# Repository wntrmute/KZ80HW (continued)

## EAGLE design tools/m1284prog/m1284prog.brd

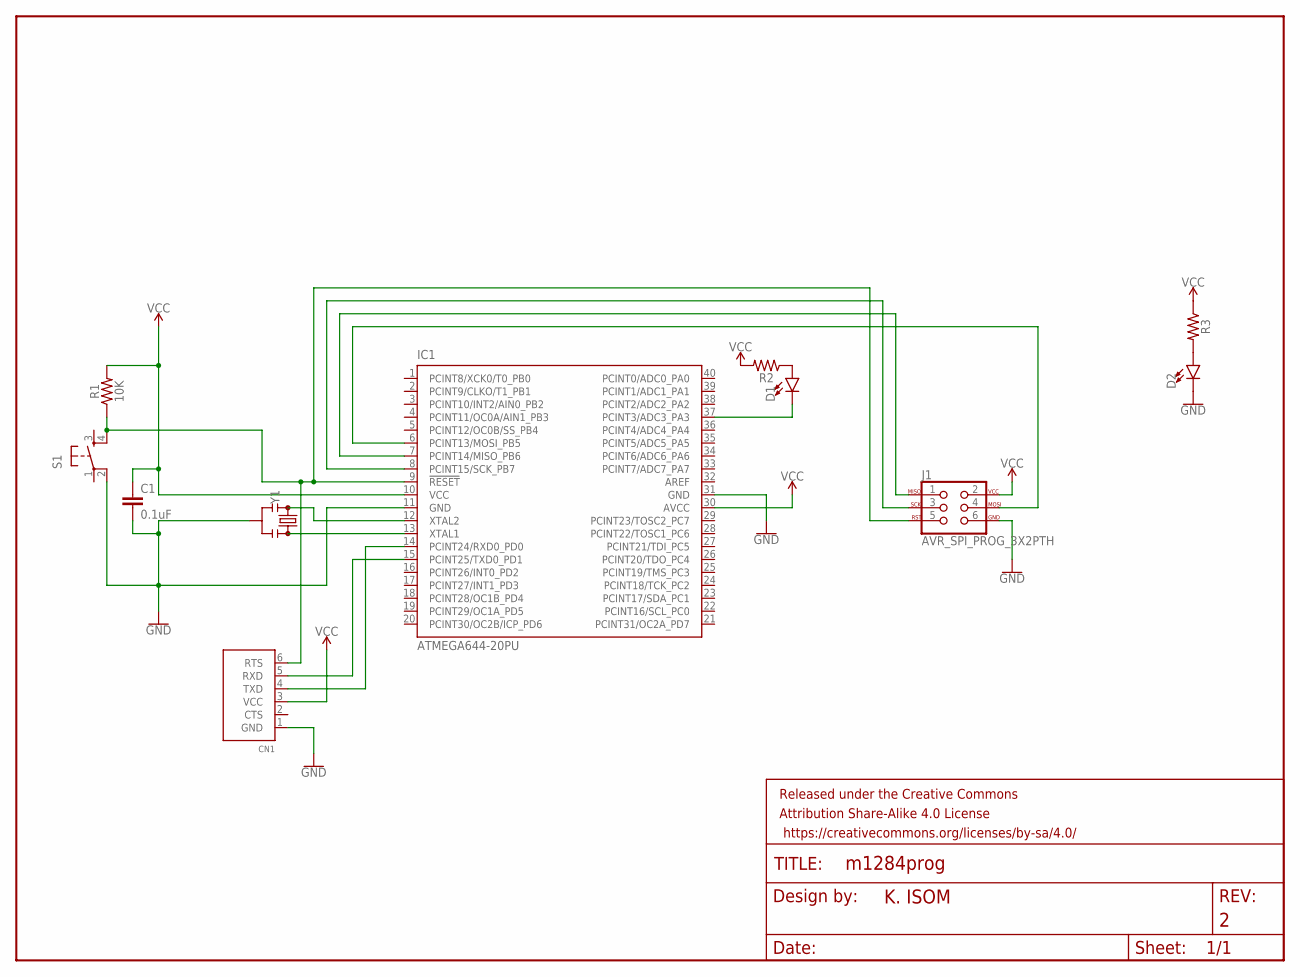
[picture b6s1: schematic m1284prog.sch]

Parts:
C1: 0.1uF; C2.5-3
CN1: FTDIUSBCABLE; 1X06_ROUND
D1, D2: LED3MM; LED_3MM
FRAME1: FRAME-LETTER; CREATIVE_COMMONS
IC1: ATMEGA644-20PU; DIL40
J1: AVR_SPI_PROG_3X2PTH; 2X3
R1: 10K; AXIAL-0.3
R2, R3: AXIAL-0.3
S1: TAC_SWITCHPTH; TACTILE-PTH
Y1: RESONATORPTH-7.6X3.8; RESONATOR-PTH-7.6X3.8

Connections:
GND: C1.2, CN1.1 (GND), D2.K (C), IC1.11 (GND), IC1.31 (GND), J1.6, S1.2, Y1.2
unnamed: IC1.12 (XTAL2), Y1.1
unnamed: IC1.13 (XTAL1), Y1.3
unnamed: IC1.6 (PCINT13/MOSI_PB5), J1.4
unnamed: CN1.6 (RTS), IC1.9 (!RESET), J1.5, R1.P$1 (1), S1.4
unnamed: IC1.7 (PCINT14/MISO_PB6), J1.1
unnamed: IC1.8 (PCINT15/SCK_PB7), J1.3
unnamed: D1.K (C), IC1.37 (PCINT3/ADC3_PA3)
unnamed: D1.A, R2.P$1 (1)
unnamed: CN1.4 (TXD), IC1.14 (PCINT24/RXD0_PD0)
unnamed: CN1.5 (RXD), IC1.15 (PCINT25/TXD0_PD1)
unnamed: D2.A, R3.P$2 (2)
VCC: C1.1, CN1.3 (VCC), IC1.10 (VCC), IC1.30 (AVCC), J1.2, R1.P$2 (2), R2.P$2 (2), R3.P$1 (1)

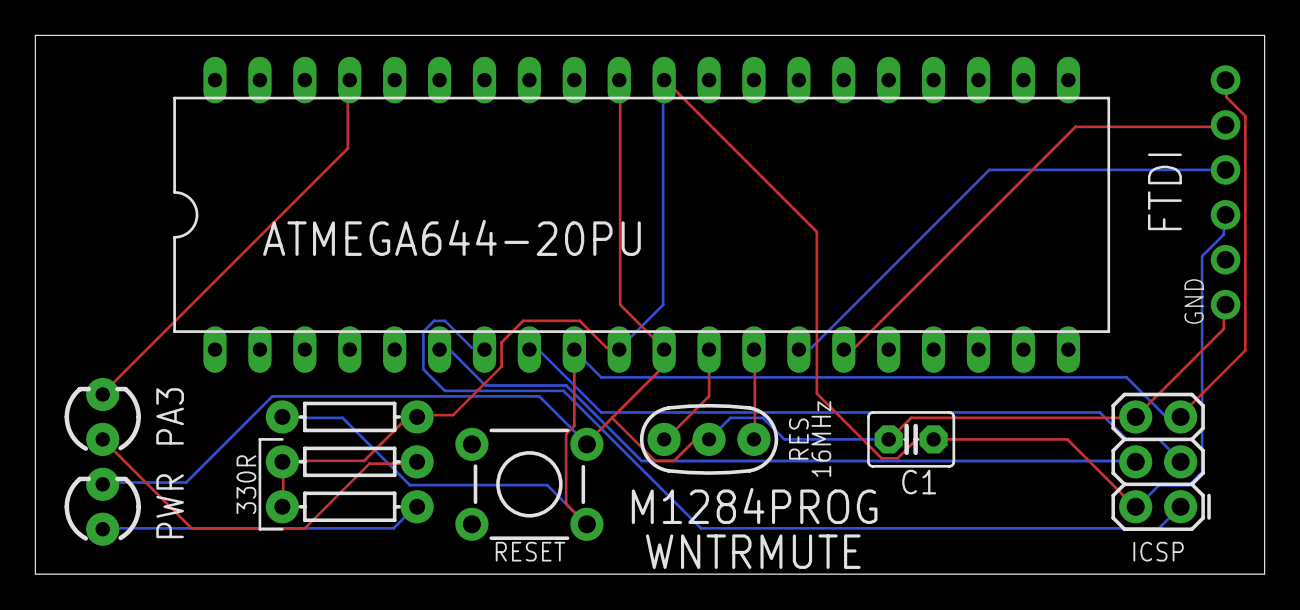
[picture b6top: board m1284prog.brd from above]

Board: 2 copper layers, 69.5 x 30.5 mm, 12 parts (0 on the bottom side), 13 nets.

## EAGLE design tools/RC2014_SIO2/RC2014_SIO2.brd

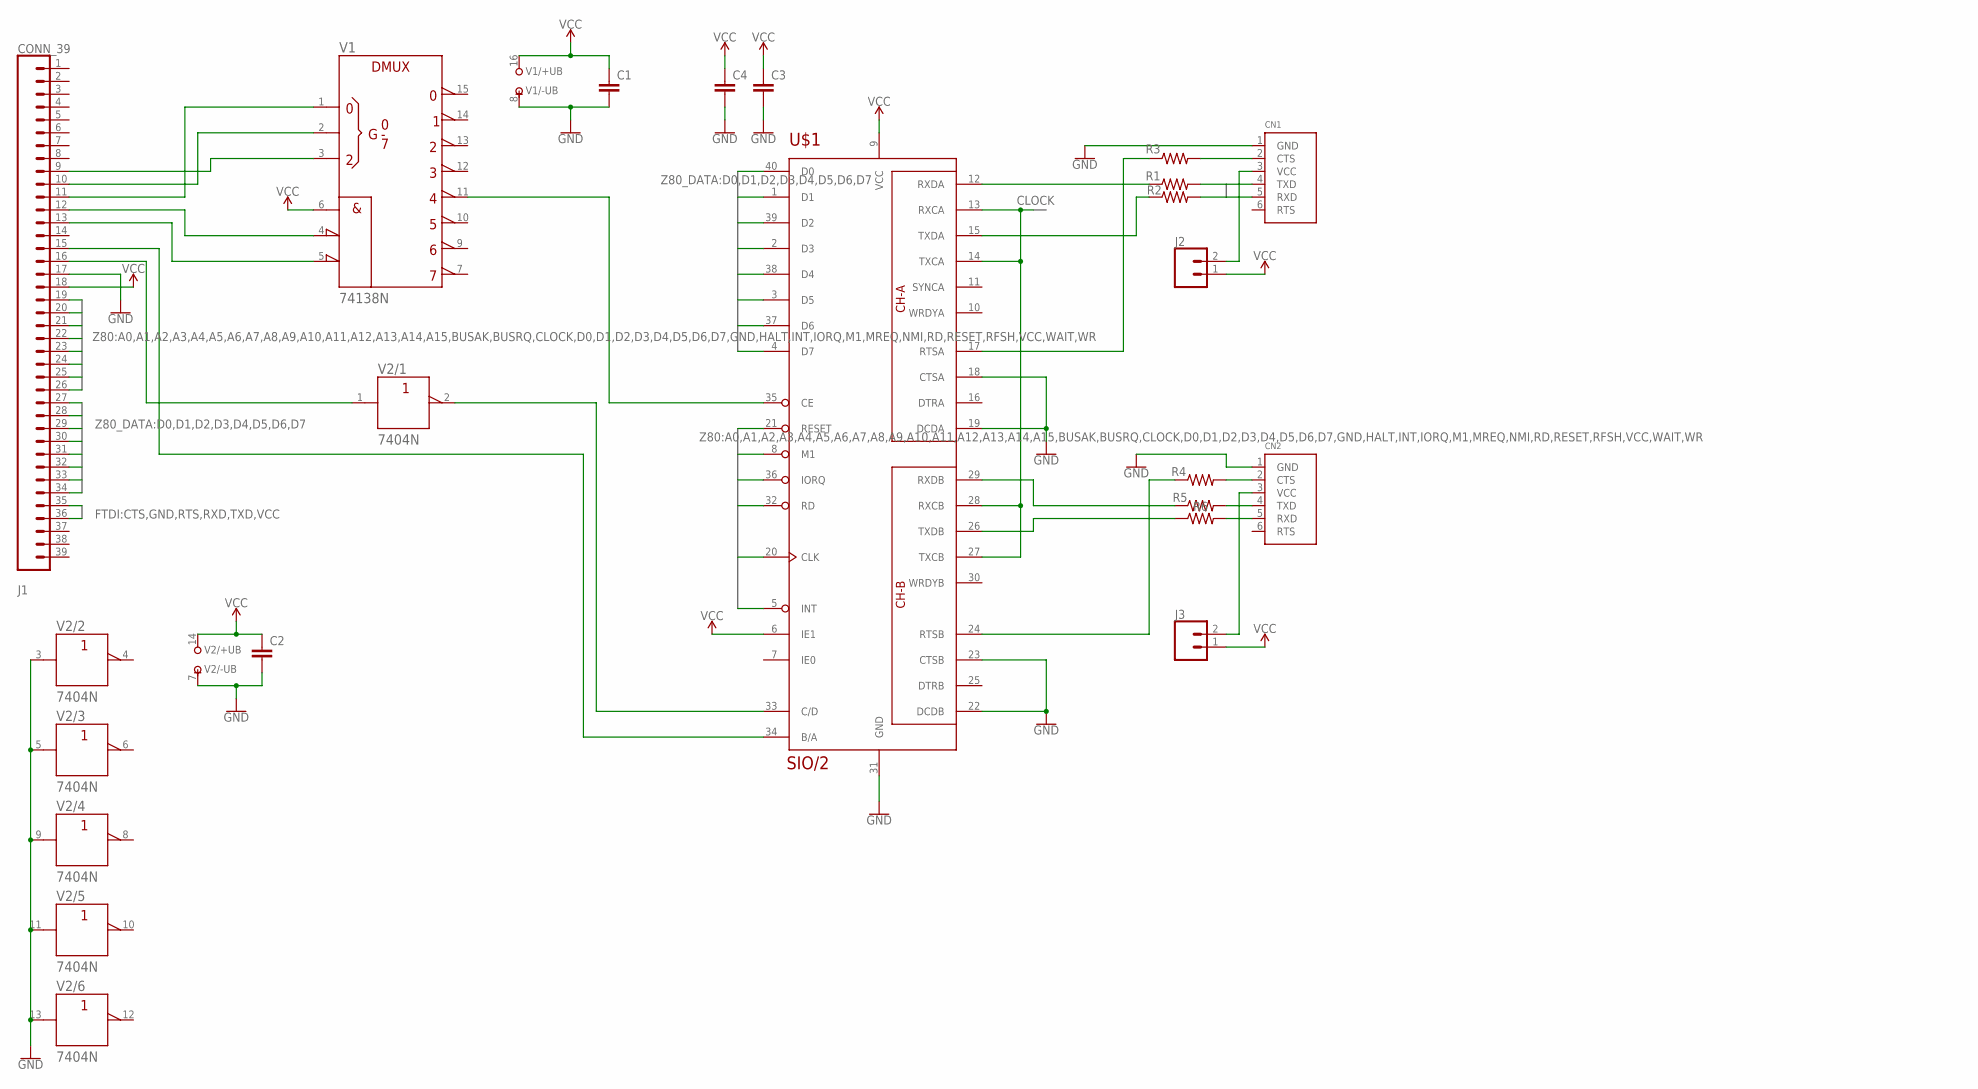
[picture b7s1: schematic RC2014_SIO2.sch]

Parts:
C1, C2, C3, C4: C2,5-3; C2.5-3
CN1, CN2: FTDIUSBCABLE; 1X06_ROUND
J1: CONN_39; 1X39
J2, J3: CONN_02; 1X02
R1, R2, R3, R4, R5, R6: AXIAL-0.3
U$1: SIO/2; DIL40
V1: 74138N; DIL16
V2: 7404N; DIL14

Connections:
CLOCK: J1.21, U$1.13 (RXCA), U$1.14 (TXCA), U$1.20 (CLK), U$1.27 (TXCB), U$1.28 (RXCB)
D0: J1.27, U$1.40 (D0)
D1: J1.28, U$1.1 (D1)
D2: J1.29, U$1.39 (D2)
D3: J1.30, U$1.2 (D3)
D4: J1.31, U$1.38 (D4)
D5: J1.32, U$1.3 (D5)
D6: J1.33, U$1.37 (D6)
D7: J1.34, U$1.4 (D7)
GND: C1.2, C2.2, C3.2, C4.2, CN1.1 (GND), CN2.1 (GND), J1.17, U$1.18 (CTSA), U$1.19 (DCDA), U$1.22 (DCDB), U$1.23 (CTSB), U$1.31 (GND), V1.8 (-UB), V2.3 (A), V2.5 (A), V2.7 (-UB), V2.9 (A), V2.11 (A), V2.13 (A)
INT: J1.22, U$1.5 (INT)
IORQ: J1.26, U$1.36 (IORQ)
M1: J1.19, U$1.8 (M1)
MREQ: J1.23
unnamed: J1.16, V2.1 (A)
unnamed: J1.15, U$1.34 (B/A)
unnamed: U$1.33 (C/D), V2.2 (Y)
unnamed: J1.13, V1.5 (!G2B)
unnamed: J1.12, V1.4 (!G2A)
unnamed: R1.P$1 (1), U$1.12 (RXDA)
unnamed: J1.11, V1.1 (A)
unnamed: J1.10, V1.2 (B)
unnamed: J1.9, V1.3 (C)
unnamed: U$1.35 (CE), V1.11 (Y4)
unnamed: R2.P$1 (1), U$1.15 (TXDA)
unnamed: R3.P$1 (1), U$1.17 (RTSA)
unnamed: CN1.2 (CTS), R3.P$2 (2)
unnamed: CN2.2 (CTS), R4.P$2 (2)
unnamed: CN2.4 (TXD), R5.P$2 (2)
unnamed: CN2.5 (RXD), R6.P$2 (2)
unnamed: R5.P$1 (1), U$1.29 (RXDB)
unnamed: R6.P$1 (1), U$1.26 (TXDB)
unnamed: CN1.3 (VCC), J2.2
unnamed: R4.P$1 (1), U$1.24 (RTSB)
unnamed: CN2.3 (VCC), J3.2
RD: J1.25, U$1.32 (RD)
RESET: J1.20, U$1.21 (RESET)
RXD: CN1.4 (TXD), J1.36, R1.P$2 (2)
TXD: CN1.5 (RXD), J1.35, R2.P$2 (2)
VCC: C1.1, C2.1, C3.1, C4.1, J1.18, J2.1, J3.1, U$1.6 (IE1), U$1.9 (VCC), V1.6 (G1), V1.16 (+UB), V2.14 (+UB)
WR: J1.24

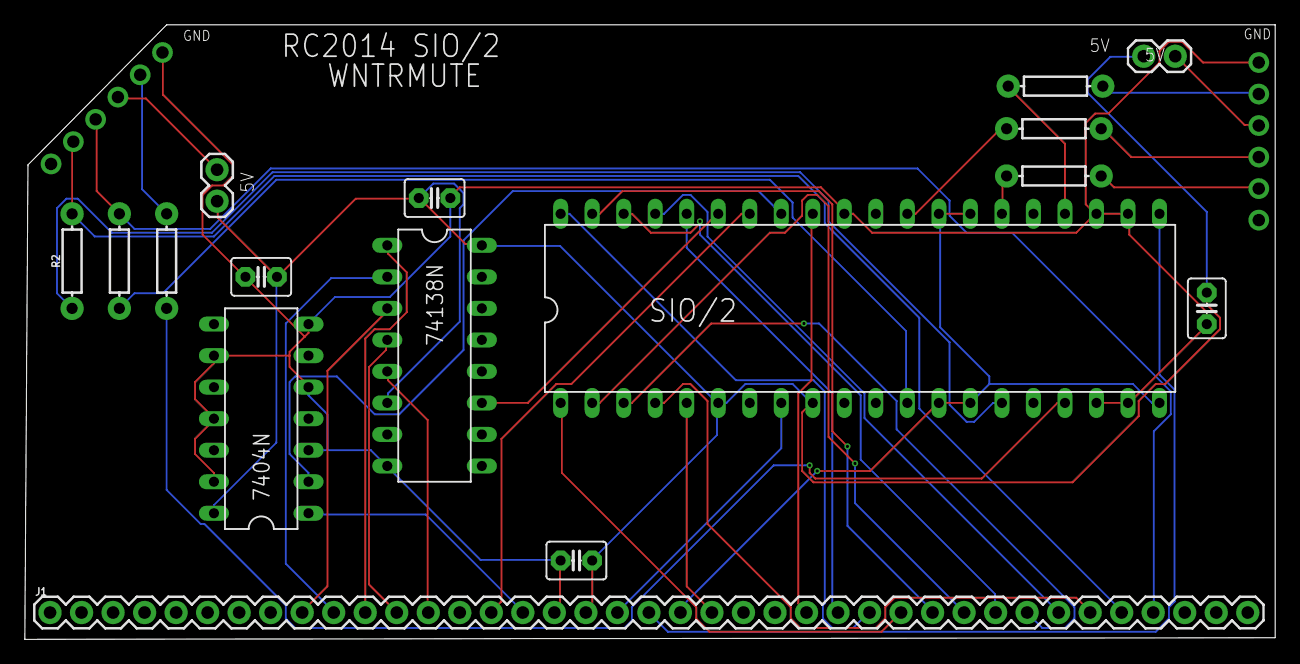
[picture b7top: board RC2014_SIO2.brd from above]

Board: 2 copper layers, 100.8 x 49.5 mm, 18 parts (0 on the bottom side), 39 nets.

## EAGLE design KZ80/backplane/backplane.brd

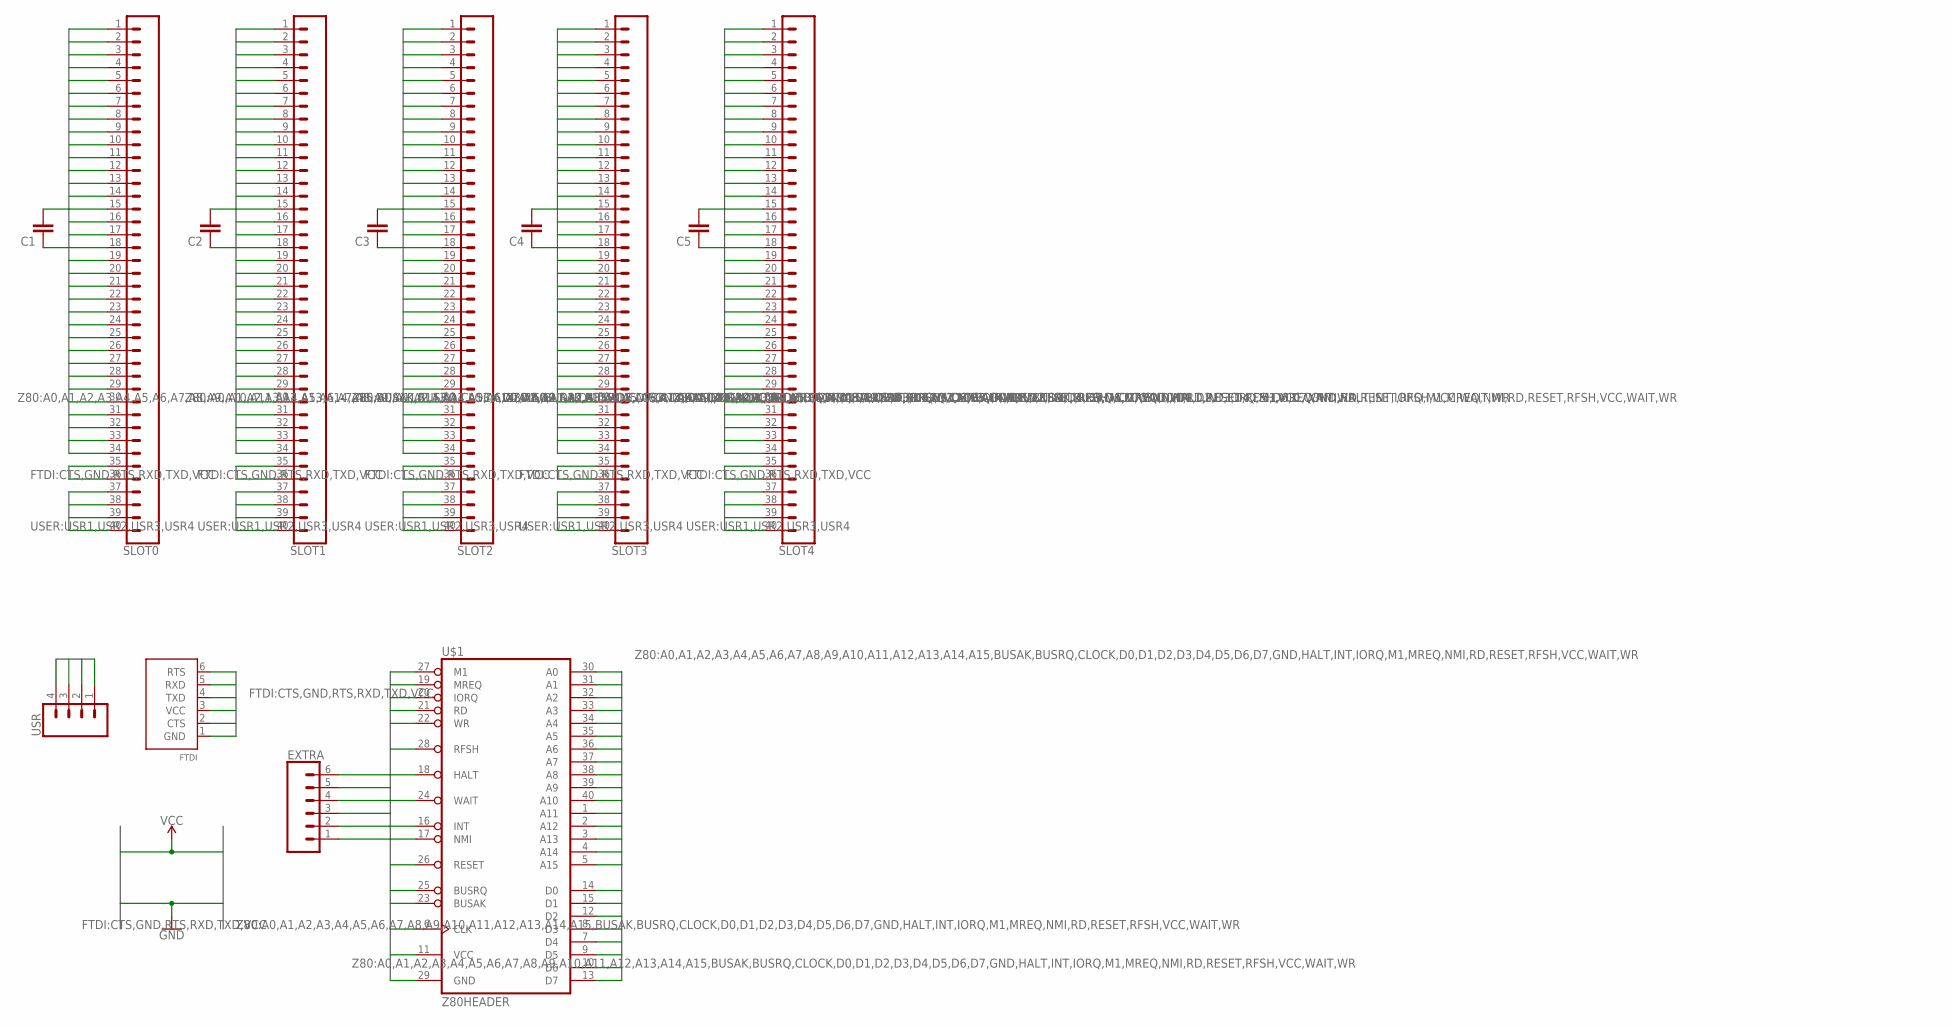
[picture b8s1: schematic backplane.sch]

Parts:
C1, C2, C3, C4, C5: C2,5-3; C2.5-3
EXTRA: CONN_06LOCK; 1X06_LOCK
FTDI: FTDIUSBCABLE; 1X06_ROUND
SLOT0, SLOT1, SLOT2, SLOT3, SLOT4: CONN_40; 1X40
U$1: Z80HEADER; 2X20
USR: CONN_04PTH; 1X04

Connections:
A0: SLOT0.16, SLOT1.16, SLOT2.16, SLOT3.16, SLOT4.16, U$1.30 (A0)
A1: SLOT0.15, SLOT1.15, SLOT2.15, SLOT3.15, SLOT4.15, U$1.31 (A1)
A2: SLOT0.14, SLOT1.14, SLOT2.14, SLOT3.14, SLOT4.14, U$1.32 (A2)
A3: SLOT0.13, SLOT1.13, SLOT2.13, SLOT3.13, SLOT4.13, U$1.33 (A3)
A4: SLOT0.12, SLOT1.12, SLOT2.12, SLOT3.12, SLOT4.12, U$1.34 (A4)
A5: SLOT0.11, SLOT1.11, SLOT2.11, SLOT3.11, SLOT4.11, U$1.35 (A5)
A6: SLOT0.10, SLOT1.10, SLOT2.10, SLOT3.10, SLOT4.10, U$1.36 (A6)
A7: SLOT0.9, SLOT1.9, SLOT2.9, SLOT3.9, SLOT4.9, U$1.37 (A7)
A8: SLOT0.8, SLOT1.8, SLOT2.8, SLOT3.8, SLOT4.8, U$1.38 (A8)
A9: SLOT0.7, SLOT1.7, SLOT2.7, SLOT3.7, SLOT4.7, U$1.39 (A9)
A10: SLOT0.6, SLOT1.6, SLOT2.6, SLOT3.6, SLOT4.6, U$1.40 (A10)
A11: SLOT0.5, SLOT1.5, SLOT2.5, SLOT3.5, SLOT4.5, U$1.1 (A11)
A12: SLOT0.4, SLOT1.4, SLOT2.4, SLOT3.4, SLOT4.4, U$1.2 (A12)
A13: SLOT0.3, SLOT1.3, SLOT2.3, SLOT3.3, SLOT4.3, U$1.3 (A13)
A14: SLOT0.2, SLOT1.2, SLOT2.2, SLOT3.2, SLOT4.2, U$1.4 (A14)
A15: SLOT0.1, SLOT1.1, SLOT2.1, SLOT3.1, SLOT4.1, U$1.5 (A15)
BUSAK: EXTRA.6, U$1.23 (BUSAK)
BUSRQ: EXTRA.5, U$1.25 (BUSRQ)
CLOCK: SLOT0.21, SLOT1.21, SLOT2.21, SLOT3.21, SLOT4.21, U$1.6 (CLK)
CTS: FTDI.2 (CTS)
D0: SLOT0.27, SLOT1.27, SLOT2.27, SLOT3.27, SLOT4.27, U$1.14 (D0)
D1: SLOT0.28, SLOT1.28, SLOT2.28, SLOT3.28, SLOT4.28, U$1.15 (D1)
D2: SLOT0.29, SLOT1.29, SLOT2.29, SLOT3.29, SLOT4.29, U$1.12 (D2)
D3: SLOT0.30, SLOT1.30, SLOT2.30, SLOT3.30, SLOT4.30, U$1.8 (D3)
D4: SLOT0.31, SLOT1.31, SLOT2.31, SLOT3.31, SLOT4.31, U$1.7 (D4)
D5: SLOT0.32, SLOT1.32, SLOT2.32, SLOT3.32, SLOT4.32, U$1.9 (D5)
D6: SLOT0.33, SLOT1.33, SLOT2.33, SLOT3.33, SLOT4.33, U$1.10 (D6)
D7: SLOT0.34, SLOT1.34, SLOT2.34, SLOT3.34, SLOT4.34, U$1.13 (D7)
GND: C1.1, C2.1, C3.1, C4.1, C5.1, FTDI.1 (GND), SLOT0.17, SLOT1.17, SLOT2.17, SLOT3.17, SLOT4.17, U$1.29 (GND)
HALT: EXTRA.3, U$1.18 (HALT)
INT: SLOT0.22, SLOT1.22, SLOT2.22, SLOT3.22, SLOT4.22, U$1.16 (INT)
IORQ: SLOT0.26, SLOT1.26, SLOT2.26, SLOT3.26, SLOT4.26, U$1.20 (IORQ)
M1: SLOT0.19, SLOT1.19, SLOT2.19, SLOT3.19, SLOT4.19, U$1.27 (M1)
MREQ: SLOT0.23, SLOT1.23, SLOT2.23, SLOT3.23, SLOT4.23, U$1.19 (MREQ)
NMI: EXTRA.2, U$1.17 (NMI)
RD: SLOT0.25, SLOT1.25, SLOT2.25, SLOT3.25, SLOT4.25, U$1.21 (RD)
RESET: SLOT0.20, SLOT1.20, SLOT2.20, SLOT3.20, SLOT4.20, U$1.26 (RESET)
RFSH: EXTRA.1, U$1.28 (RFSH)
RTS: FTDI.6 (RTS)
RXD: FTDI.5 (RXD), SLOT0.36, SLOT1.36, SLOT2.36, SLOT3.36, SLOT4.36
TXD: FTDI.4 (TXD), SLOT0.35, SLOT1.35, SLOT2.35, SLOT3.35, SLOT4.35
USR1: SLOT0.37, SLOT1.37, SLOT2.37, SLOT3.37, SLOT4.37, USR.1
USR2: SLOT0.38, SLOT1.38, SLOT2.38, SLOT3.38, SLOT4.38, USR.2
USR3: SLOT0.39, SLOT1.39, SLOT2.39, SLOT3.39, SLOT4.39, USR.3
USR4: SLOT0.40, SLOT1.40, SLOT2.40, SLOT3.40, SLOT4.40, USR.4
VCC: C1.2, C2.2, C3.2, C4.2, C5.2, FTDI.3 (VCC), SLOT0.18, SLOT1.18, SLOT2.18, SLOT3.18, SLOT4.18, U$1.11 (VCC)
WAIT: EXTRA.4, U$1.24 (WAIT)
WR: SLOT0.24, SLOT1.24, SLOT2.24, SLOT3.24, SLOT4.24, U$1.22 (WR)

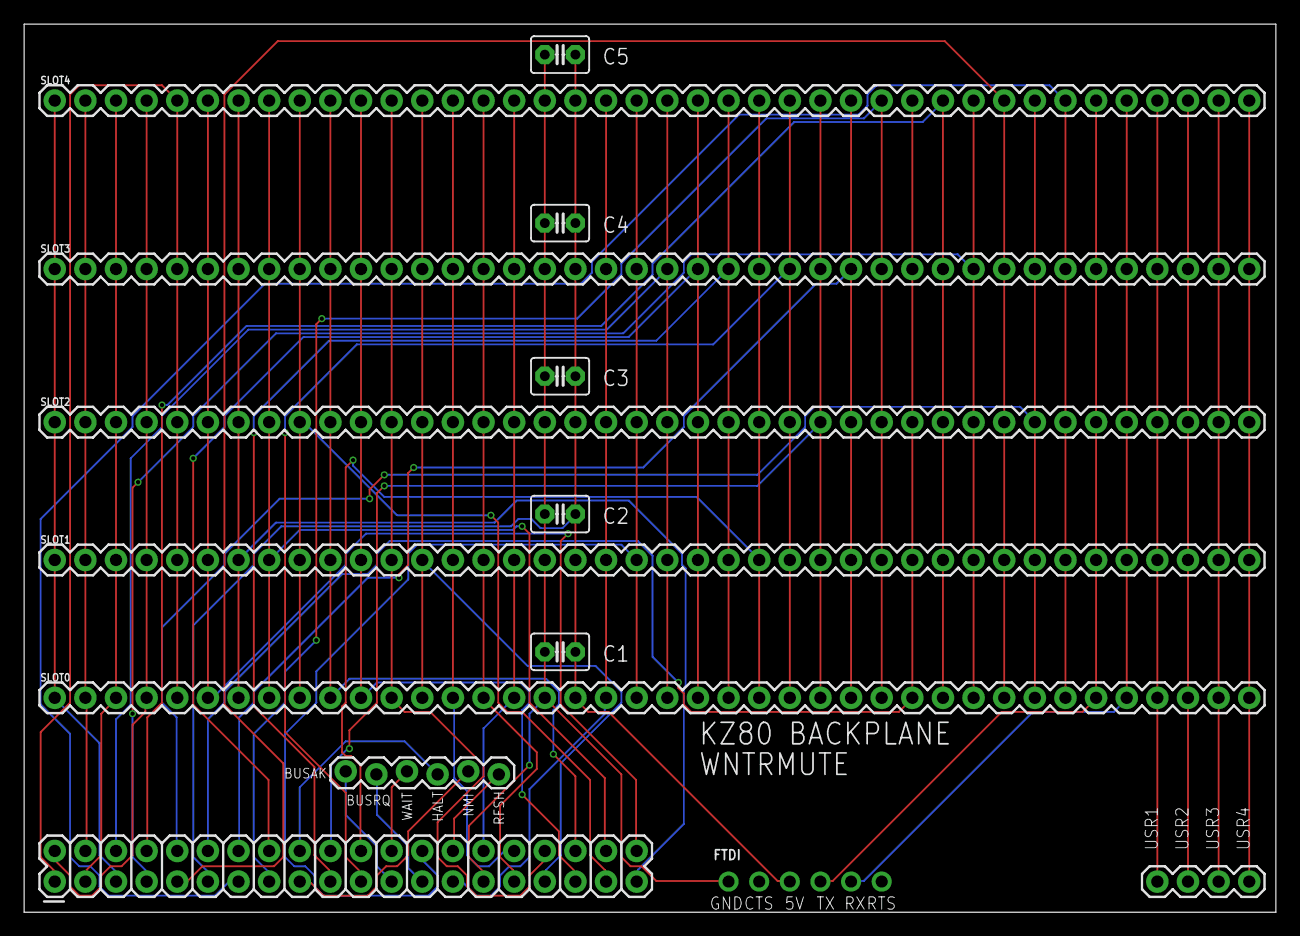
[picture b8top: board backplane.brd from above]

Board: 2 copper layers, 103.8 x 73.7 mm, 14 parts (0 on the bottom side), 46 nets.

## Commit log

2019-09-19 Initial import.
2019-09-26 Updating silk screens.
    Some parts were labeled in the tValues layer, not the tPlace
    layer, so they ended up not being printed in the final board.
2019-10-01 Update several tool boards.
    + AEPRO had the wrong socket size; the ZIF footprint was for
    a narrow 28-pin DIP.
    + AEPRO was missing an inverter on the LEDs.
    + M328PGM had a serial line tied to RST: any attempt at using the
    UART caused the board to reset.
    + M1284PGM had no silkscreen markings to identify the board.
2019-10-02 updating lib
2019-10-02 Add SIO/2 board.
2019-10-02 Update docs.
2019-10-02 Fix UART issues in programmers.
2019-10-02 Add 5140 keyboard to library.
2019-10-03 Fix UART lines on AEPRO.
2019-10-03 Tentative serial console schematic.
2019-10-05 mainboard: move RAM around
    This moves the RAM chips to give more clearance to the ROM chip, e.g
    to make swappung it out easier.
2019-10-05 sioboard: adjust layout and add ground plane.
2019-10-08 sioboard: break out interrupt priority pins.
2019-10-08 sioboard: update silkscreen.
2019-10-09 sioboard: silkscreen updates.
2019-10-09 Add almo, an arduino lora modem.
2019-10-13 AEPRO rev 7
